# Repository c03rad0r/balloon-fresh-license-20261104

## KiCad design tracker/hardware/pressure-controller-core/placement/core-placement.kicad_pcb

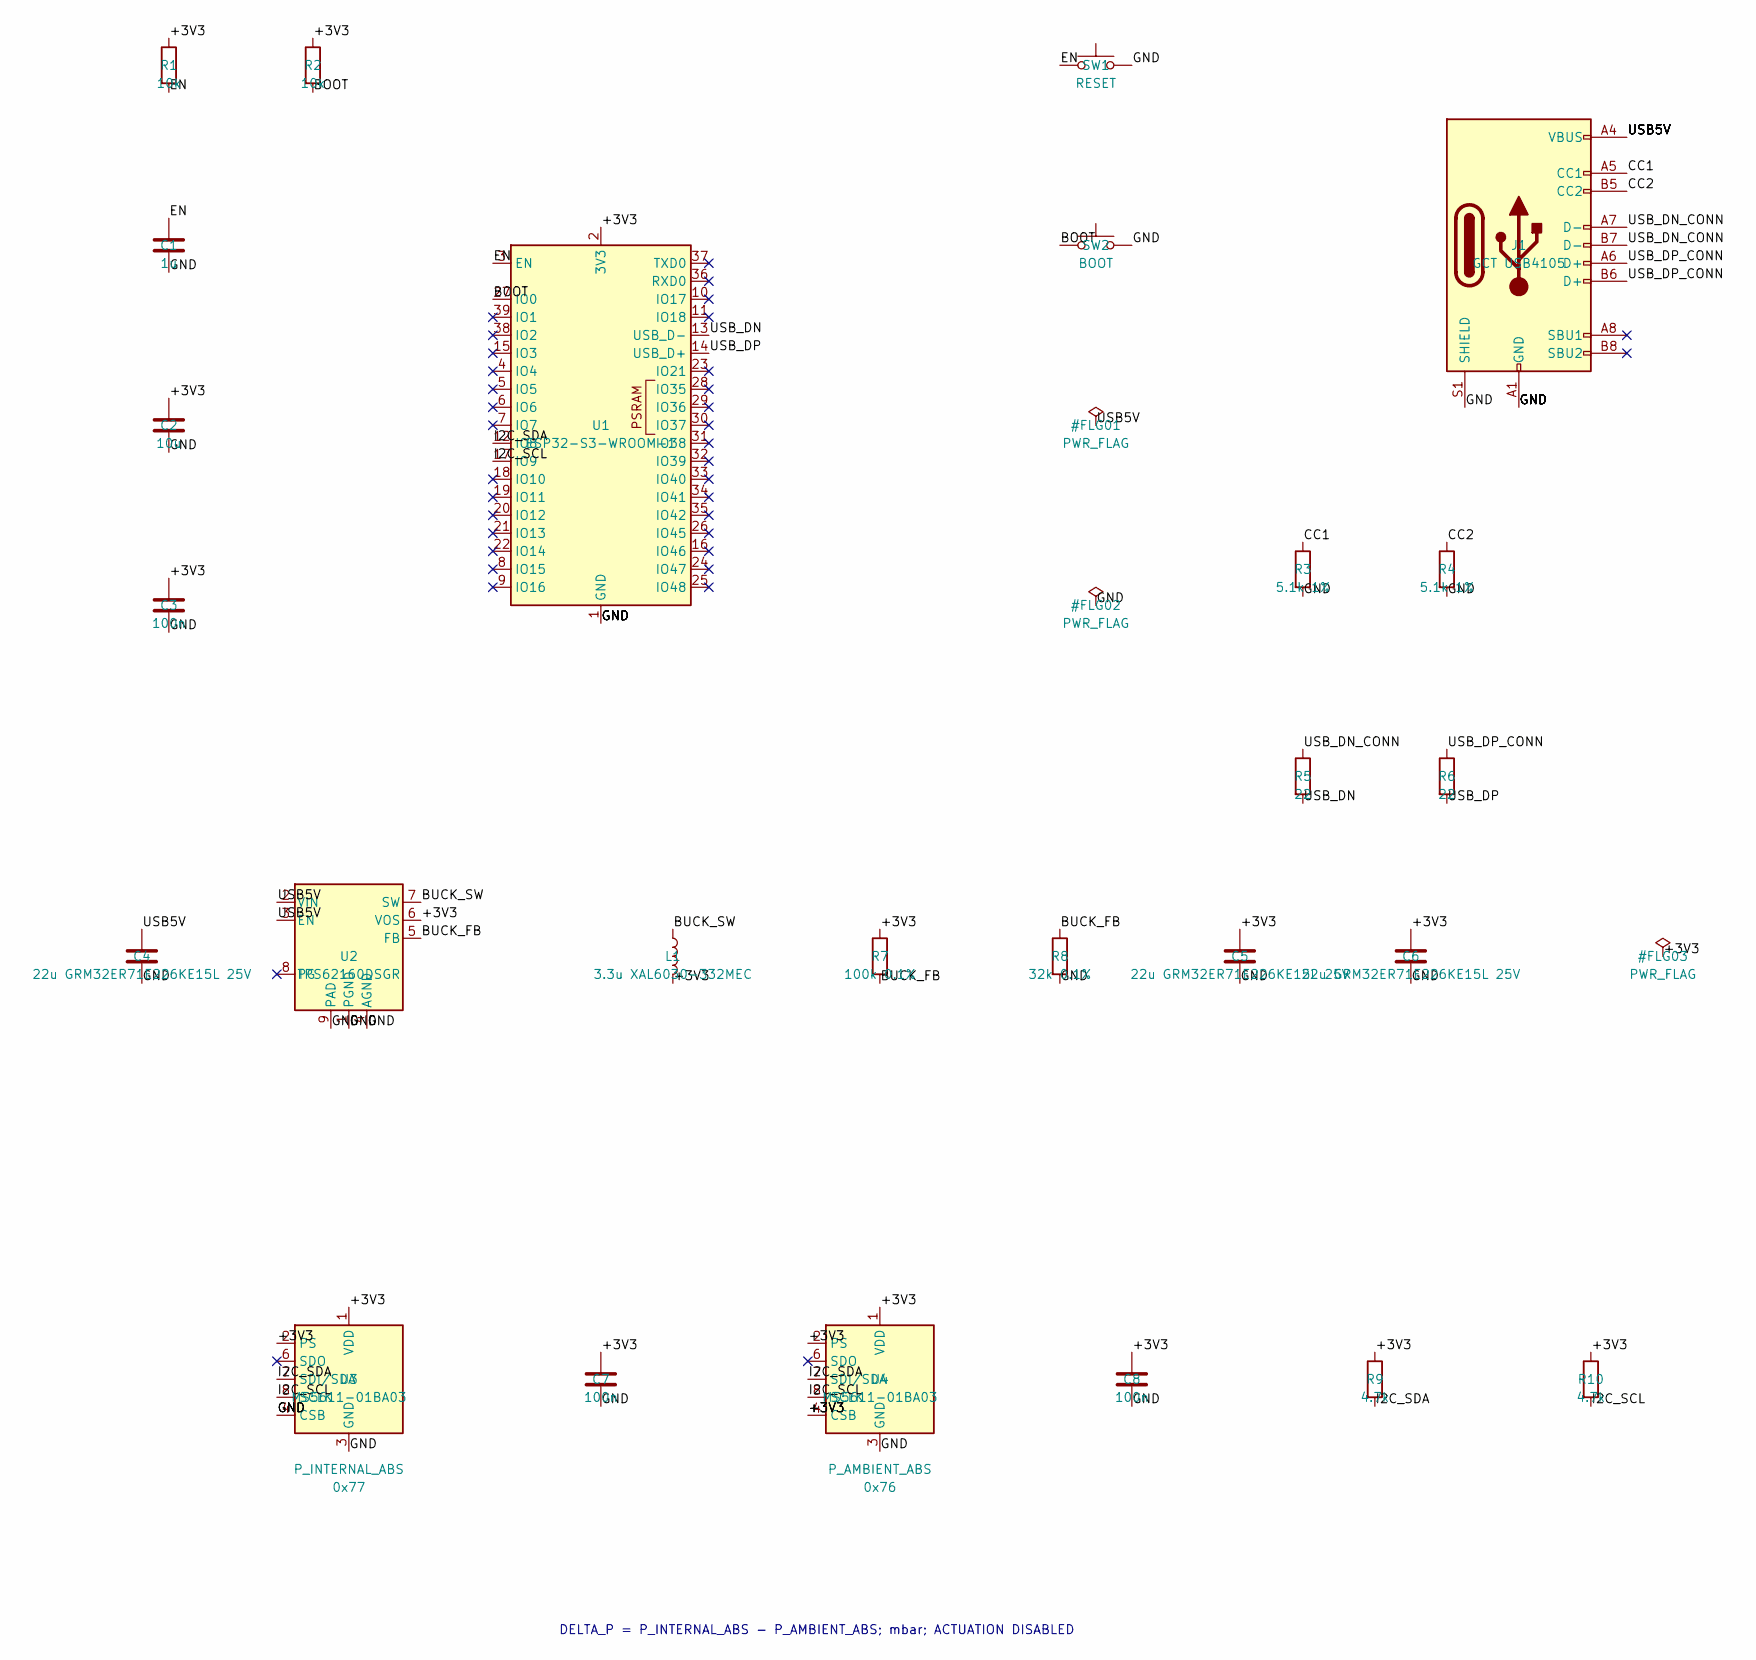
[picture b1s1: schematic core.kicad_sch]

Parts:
C1: 1u; C_0603_1608Metric
C2: 10u; C_0603_1608Metric
C3, C7, C8: 100n; C_0603_1608Metric
C4, C5, C6: 22u GRM32ER71E226KE15L 25V; C_1210_3225Metric
J1: GCT USB4105; USB_C_Receptacle_GCT_USB4105-xx-A_16P_TopMnt_Horizontal
L1: 3.3u XAL6030-332MEC; L_Coilcraft_XAL6030-XXX
R1, R2: 10k; R_0603_1608Metric
R3, R4: 5.1k 1%; R_0603_1608Metric
R5, R6: 22; R_0603_1608Metric
R7: 100k 0.1%; R_0603_1608Metric
R8: 32k 0.1%; R_0603_1608Metric
R9, R10: 4.7k; R_0603_1608Metric
SW1: RESET; SW_SPST_TL3342
SW2: BOOT; SW_SPST_TL3342
U1: ESP32-S3-WROOM-1
U2: TPS62160DSGR; WSON-8-1EP_2x2mm_P0.5mm_EP0.9x1.6mm_ThermalVias
U3, U4: MS5611-01BA03; MS5611-01BA03_TE_Recommended

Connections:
/+3V3: C2.1, C3.1, C5.1, C6.1, C7.1, C8.1, L1.2, R1.1, R2.1, R7.1, R9.1, R10.1, U1.2 (3V3), U2.6 (VOS), U3.1 (VDD), U3.2 (PS), U4.1 (VDD), U4.2 (PS), U4.4 (CSB), U4.5 (CSB)
/BOOT: R2.2, SW2.1, U1.27 (IO0)
/BUCK_FB: R7.2, R8.1, U2.5 (FB)
/BUCK_SW: L1.1, U2.7 (SW)
/CC1: J1.A5 (CC1), R3.1
/CC2: J1.B5 (CC2), R4.1
/EN: C1.1, R1.2, SW1.1, U1.3 (EN)
/GND: C1.2, C2.2, C3.2, C4.2, C5.2, C6.2, C7.2, C8.2, J1.A1 (GND), J1.A12 (GND), J1.B1 (GND), J1.B12 (GND), J1.S1 (SHIELD), R3.2, R4.2, R8.2, SW1.2, SW2.2, U1.1 (GND), U1.40 (GND), U1.41 (GND), U2.1 (PGND), U2.4 (AGND), U2.9 (PAD), U3.3 (GND), U3.4 (CSB), U3.5 (CSB), U4.3 (GND)
/I2C_SCL: R10.2, U1.17 (IO9), U3.8 (SCLK), U4.8 (SCLK)
/I2C_SDA: R9.2, U1.12 (IO8), U3.7 (SDI/SDA), U4.7 (SDI/SDA)
/USB5V: C4.1, J1.A4 (VBUS), J1.A9 (VBUS), J1.B4 (VBUS), J1.B9 (VBUS), U2.2 (VIN), U2.3 (EN)
/USB_DN: R5.2, U1.13 (USB_D-)
/USB_DN_CONN: J1.A7 (D-), J1.B7 (D-), R5.1
/USB_DP: R6.2, U1.14 (USB_D+)
/USB_DP_CONN: J1.A6 (D+), J1.B6 (D+), R6.1

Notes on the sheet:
DELTA_P = P_INTERNAL_ABS - P_AMBIENT_ABS; mbar; ACTUATION DISABLED

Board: 2 copper layers, 26 parts (0 on the bottom side), 15 nets, no tracks yet.

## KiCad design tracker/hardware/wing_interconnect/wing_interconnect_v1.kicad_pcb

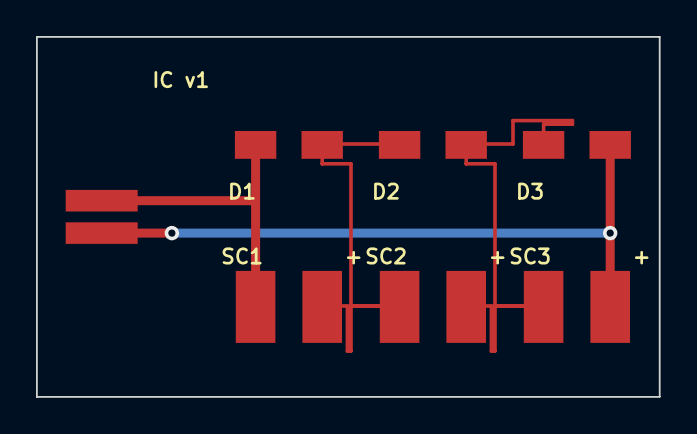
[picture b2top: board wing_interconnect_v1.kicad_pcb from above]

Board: 2 copper layers, 34.6 x 20.0 mm, 7 parts (0 on the bottom side), 4 nets.

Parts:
D1, D2, D3: D_SMA_Wing
J1: Tab_2P
SC1, SC2, SC3: SolarTail_2P

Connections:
SOLAR_MID1: D1.2, D2.1, SC1.2, SC2.1
SOLAR_MID2: D2.2, D3.1, SC2.2, SC3.1
SOLAR_N: D3.2, J1.2, SC3.2
SOLAR_P: D1.1, J1.1, SC1.1
